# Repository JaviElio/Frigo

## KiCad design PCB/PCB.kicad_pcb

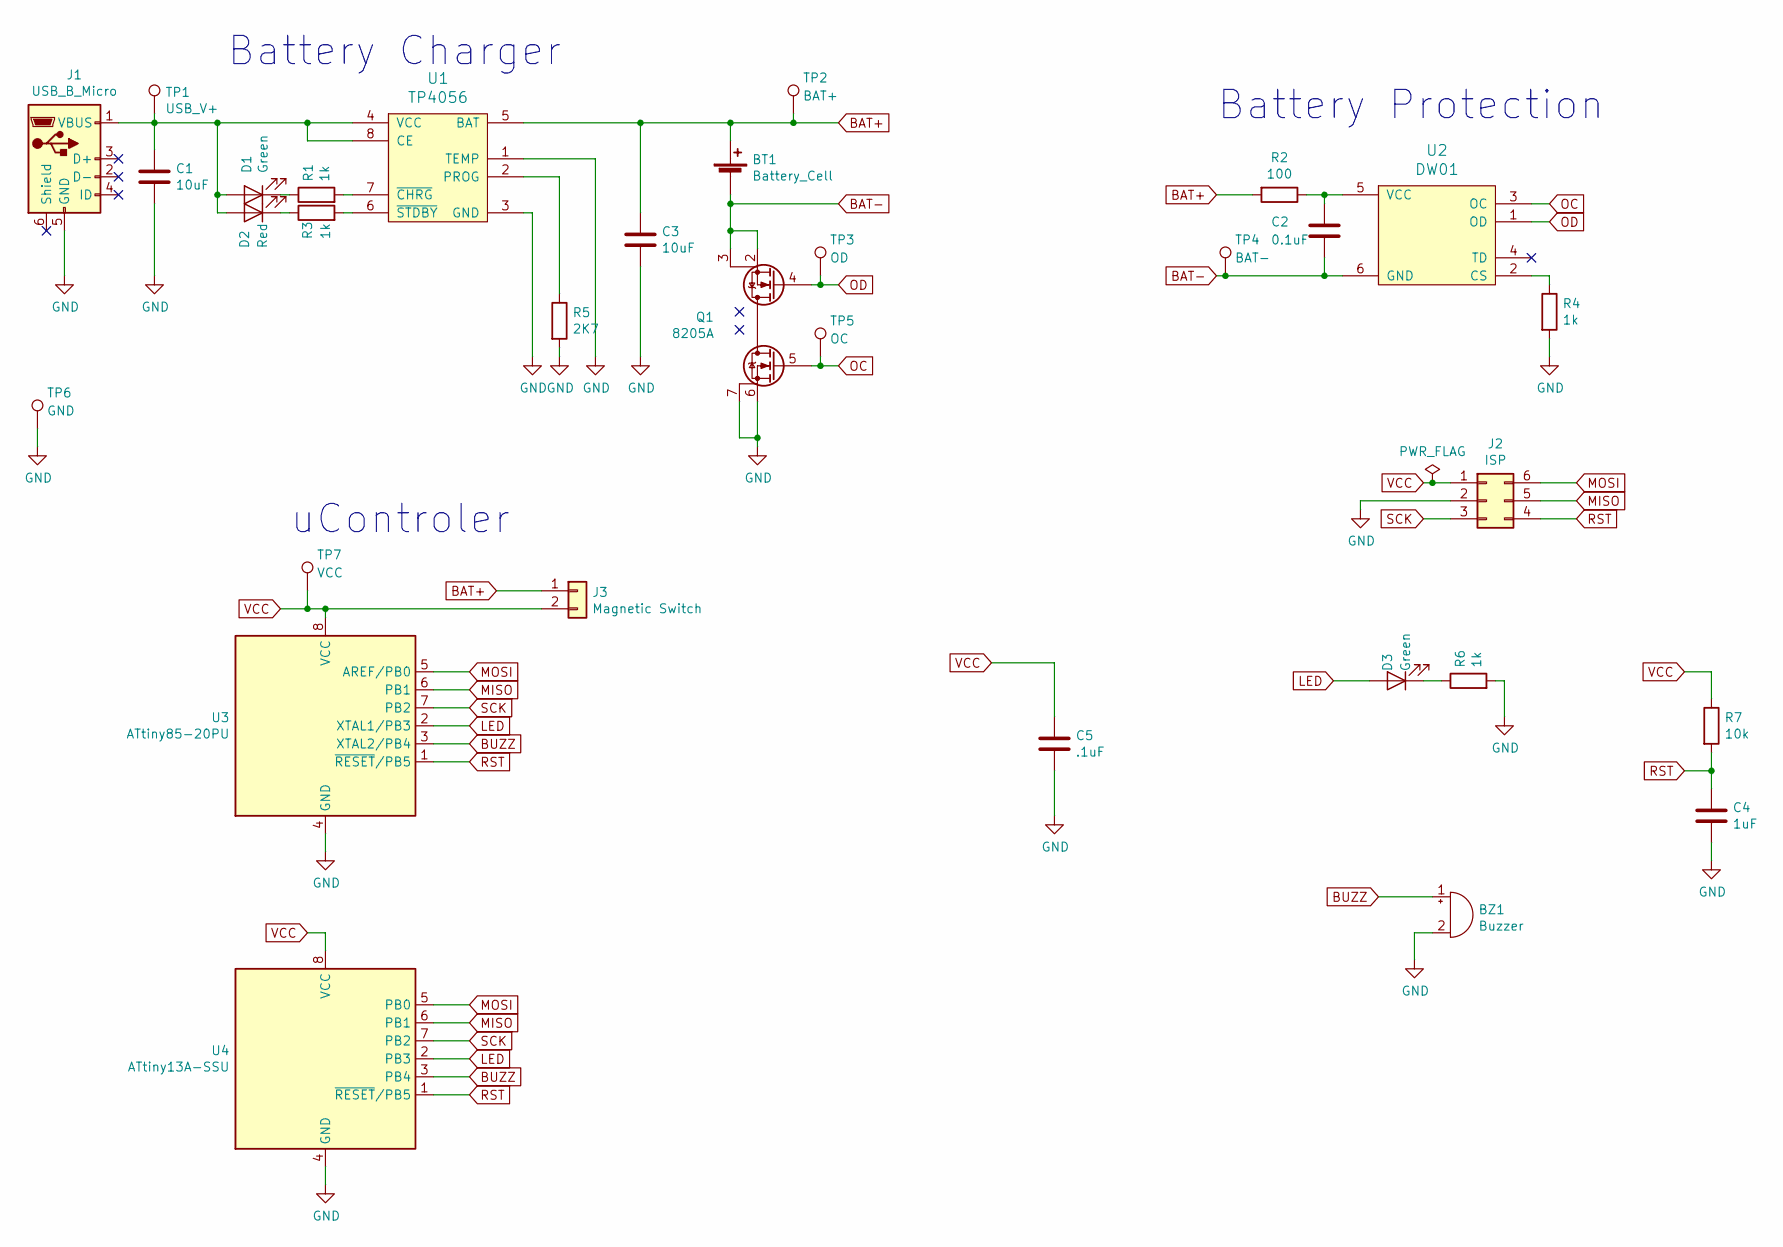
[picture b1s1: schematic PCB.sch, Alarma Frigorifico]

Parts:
BT1: Battery_Cell; PinHeader_1x02_P2.54mm_Vertical
BZ1: Buzzer; TestPoint_2Pads_Pitch2.54mm_Drill0.8mm
C1: 10uF; C_0805_2012Metric_Pad1.15x1.40mm_HandSolder
C2: 0.1uF; C_0805_2012Metric
C3: 10uF; C_0805_2012Metric
C4: 1uF; C_0805_2012Metric
C5: .1uF; C_0805_2012Metric_Pad1.15x1.40mm_HandSolder
D1: Green; LED_0805_2012Metric_Pad1.15x1.40mm_HandSolder
D2: Red; LED_0805_2012Metric_Pad1.15x1.40mm_HandSolder
D3: Green; LED_D3.0mm
J1: USB_B_Micro; MicroUSB
J2: ISP; PinHeader_2x03_P1.27mm_Vertical_SMD
J3: Magnetic Switch; PinHeader_1x02_P2.54mm_Vertical
Q1: 8205A; TSSOP-8_4.4x3mm_P0.65mm
R1, R3, R4, R6: 1k; R_0805_2012Metric_Pad1.15x1.40mm_HandSolder
R2: 100; R_0805_2012Metric_Pad1.15x1.40mm_HandSolder
R5: 2K7; R_0805_2012Metric_Pad1.15x1.40mm_HandSolder
R7: 10k; R_0805_2012Metric_Pad1.15x1.40mm_HandSolder
TP1: USB_V+; TestPoint_Pad_1.0x1.0mm
TP2: BAT+; TestPoint_Pad_1.0x1.0mm
TP3: OD; TestPoint_Pad_1.0x1.0mm
TP4: BAT-; TestPoint_Pad_1.0x1.0mm
TP5: OC; TestPoint_Pad_1.0x1.0mm
TP6: GND; TestPoint_Pad_1.0x1.0mm
TP7: VCC; TestPoint_Pad_1.0x1.0mm
U1: TP4056; SOIC-8_3.9x4.9mm_P1.27mm
U2: DW01; SOT-23-6_Handsoldering
U3: ATtiny85-20PU; DIP-8_W7.62mm
U4: ATtiny13A-SSU; SOIC-8_3.9x4.9mm_P1.27mm

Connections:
BAT+: BT1.1 (+), C3.1, J3.1, R2.2, TP2.1, U1.5 (BAT)
BAT-: BT1.2 (-), C2.2, Q1.2 (S1), Q1.3 (S1), TP4.1, U2.6 (GND)
BUZZ: BZ1.1 (-), U3.3 (XTAL2/PB4), U4.3 (PB4)
GND: BZ1.2 (+), C1.2, C3.2, C4.2, C5.2, J1.5 (GND), J2.2, Q1.6 (S2), Q1.7 (S2), R4.2, R5.2, R6.2, TP6.1, U1.1 (TEMP), U1.3 (GND), U3.4 (GND), U4.4 (GND)
LED: D3.2 (A), U3.2 (XTAL1/PB3), U4.2 (PB3)
MISO: J2.5, U3.6 (PB1), U4.6 (PB1)
MOSI: J2.6, U3.5 (AREF/PB0), U4.5 (PB0)
unnamed: C1.1, D1.2 (A), D2.2 (A), J1.1 (VBUS), TP1.1, U1.4 (VCC), U1.8 (CE)
unnamed: C2.1, R2.1, U2.5 (VCC)
unnamed: D1.1 (K), R1.1
unnamed: D2.1 (K), R3.1
unnamed: D3.1 (K), R6.1
unnamed: R1.2, U1.7 (~CHRG)
unnamed: R3.2, U1.6 (~STDBY)
unnamed: R4.1, U2.2 (CS)
unnamed: R5.1, U1.2 (PROG)
OC: Q1.5 (G2), TP5.1, U2.3 (OC)
OD: Q1.4 (G1), TP3.1, U2.1 (OD)
RST: C4.1, J2.4, R7.2, U3.1 (~RESET~/PB5), U4.1 (~RESET~/PB5)
SCK: J2.3, U3.7 (PB2), U4.7 (PB2)
VCC: C5.1, J2.1, J3.2, R7.1, TP7.1, U3.8 (VCC), U4.8 (VCC)

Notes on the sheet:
Battery Charger
Battery Protection
uControler

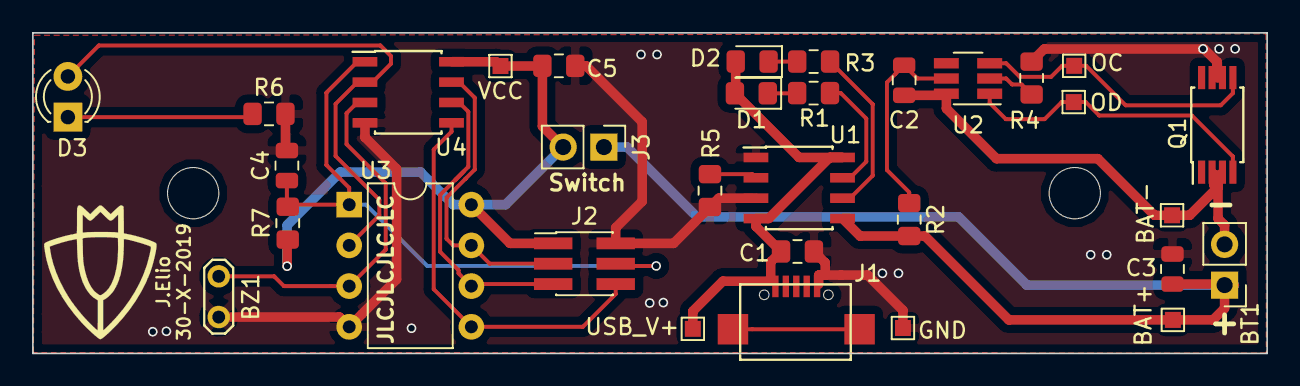
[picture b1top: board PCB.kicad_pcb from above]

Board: 2 copper layers, 77.0 x 20.0 mm, 32 parts (0 on the bottom side), 21 nets.

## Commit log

2019-11-23 First upload
